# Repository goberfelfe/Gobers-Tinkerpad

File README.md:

# Gober's Tinkerpad
My Hackpad submission!

# About
This is my first hardware project, and it took me WEEKS to finish because I had absolutely no idea what I was doing. I had to restart so many times I almost gave up, but here we are!
# Schematic
I got a bit of help from my friend setting up the schematic. I wanted a LOT of buttons, and I had no idea how to make a matrix. it all worked out (hopefully!)

# PCB
The PCB is sort of crowded since I designed a case for my first attempt and had to restart multiple times. I didn't want to redo the case.

# CAD
Here is the case for the macropad with all the other parts. I used Onshape to make the case. You can open the Onshape document [here!](https://cad.onshape.com/documents/7796dfcd00a07795a78ec31b/w/0ed4cf9bd7f3ab11e0fad6be/e/c3fea92cde887115296eb8a5?renderMode=0&uiState=6991f48789cf1a8369e0d710)

# Firmware
I used kmk for the firmware. The oled displays what mode you're using when you change it, and any other buttons show a silly Gober face. There is also an idle animation.

# BOM
Materials I used:
- 16x Cherry MX switches
- 1x 0.91 inch OLED display
- 1x Xiao RP2040
- 16x 1N4148 Diodes
- 1x 3D printed case

# Credits
Thanks to [Thegreatmewer](https://github.com/Thegreatmewer), [this video by Digikey](https://youtu.be/WU59DkI3BpQ), and the Hack Club Slack for helping me out!

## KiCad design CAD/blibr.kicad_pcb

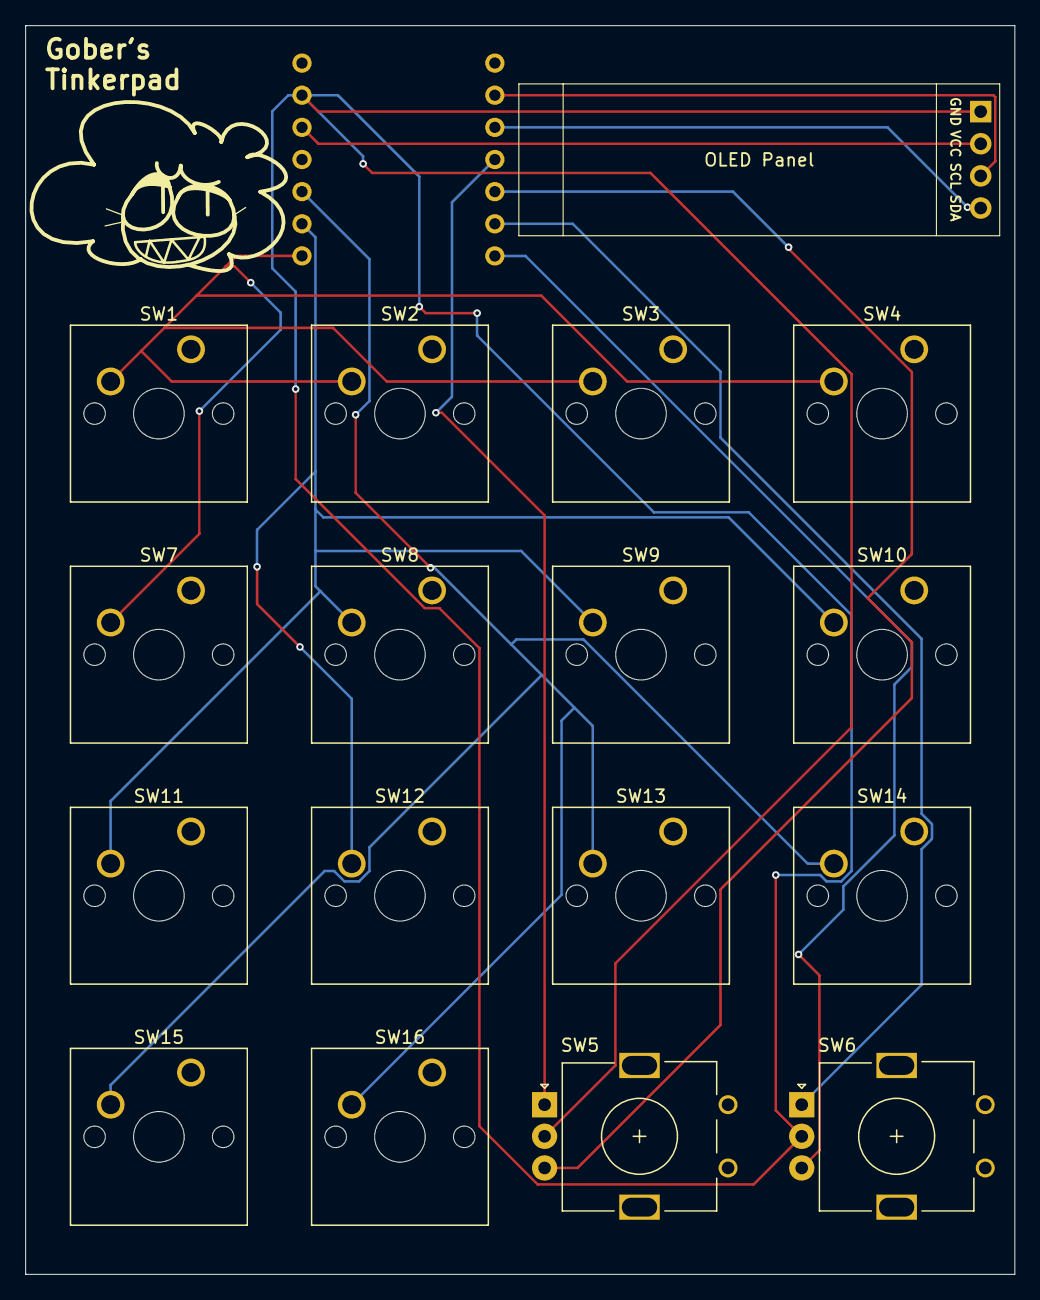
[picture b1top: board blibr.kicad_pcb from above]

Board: 2 copper layers, 78.2 x 98.7 mm, 18 parts (1 on the bottom side), 11 nets.

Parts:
J1: custom oled pins; awesome_oled
SW1, SW2, SW3, SW4, SW7, SW8, SW9, SW10, SW11, SW12, SW13, SW14, SW15, SW16: SW_Push; SW_Cherry_MX_1.00u_PCB
SW5, SW6: RotaryEncoder; RotaryEncoder_Alps_EC11E_Vertical_H20mm
U4: XIAO-RP2040-DIP

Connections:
GND: J1.1 (GND), SW5.C, SW6.C, U4.13 (GND)
unnamed: J1.3 (SCL), U4.2 (GPIO27/ADC1/A1)
unnamed: J1.4 (SDA), U4.3 (GPIO28/ADC2/A2)
unnamed: J1.2 (VCC), U4.12 (3V3)
unnamed: SW6.B, U4.7 (GPIO0/TX)
unnamed: SW1.2, SW2.2, SW3.2, SW4.2, SW7.2, U4.8 (GPIO1/RX)
unnamed: SW8.2, SW9.2, SW10.2, SW11.2, SW12.2, U4.9 (GPIO2/SCK)
unnamed: SW13.2, SW14.2, SW15.2, SW16.2, U4.10 (GPIO4/MISO)
unnamed: SW5.B, U4.5 (GPIO6/SDA)
unnamed: SW6.A, U4.6 (GPIO7/SCL)
unnamed: SW5.A, U4.4 (GPIO29/ADC3/A3)

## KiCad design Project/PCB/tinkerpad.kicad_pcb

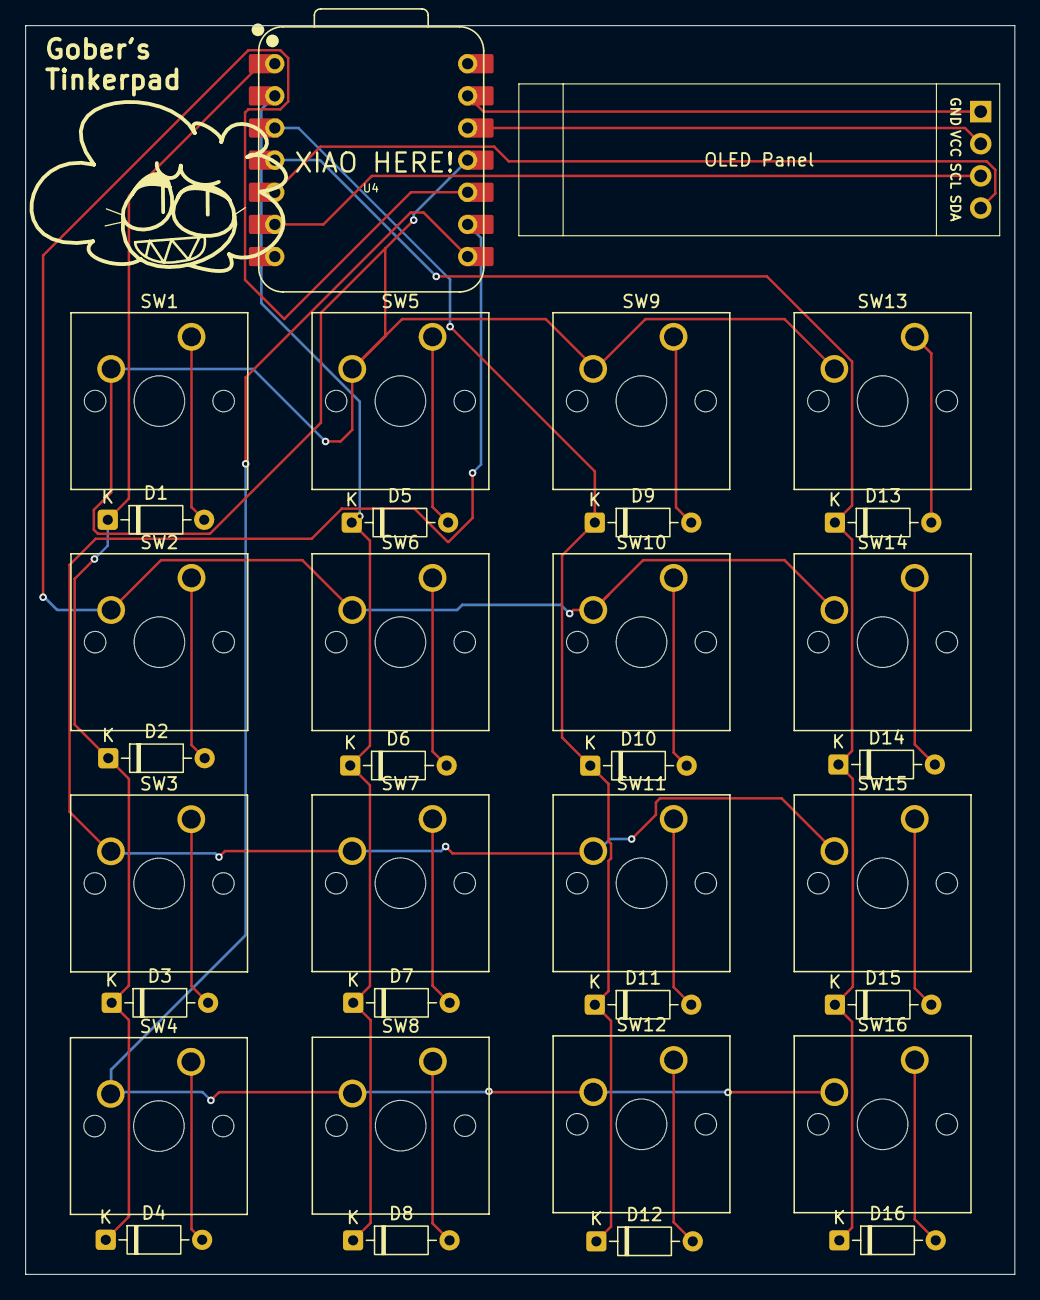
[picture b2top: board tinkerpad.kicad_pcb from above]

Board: 2 copper layers, 78.2 x 98.7 mm, 34 parts (0 on the bottom side), 28 nets.

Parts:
D1, D2, D3, D4, D5, D6, D7, D8, D9, D10, D11, D12, D13, D14, D15, D16: 1N4148; D_DO-35_SOD27_P7.62mm_Horizontal
J1: custom oled pins; awesome_oled
SW1, SW2, SW3, SW4, SW5, SW6, SW7, SW8, SW9, SW10, SW11, SW12, SW13, SW14, SW15, SW16: SW_Push; SW_Cherry_MX_1.00u_PCB
U4: XIAO-RP2040-DIP

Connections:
COL 1: SW1.2, SW5.2, SW9.2, SW13.2, U4.11 (GPIO3/MOSI)
COL 2: SW2.2, SW6.2, SW10.2, SW14.2, U4.10 (GPIO4/MISO)
COL 3: SW3.2, SW7.2, SW11.2, SW15.2, U4.9 (GPIO2/SCK)
COL 4: SW4.2, SW8.2, SW12.2, SW16.2, U4.8 (GPIO1/RX)
GND: J1.1 (GND), U4.13 (GND)
unnamed: D1.2 (A), SW1.1
unnamed: D2.2 (A), SW2.1
unnamed: D3.2 (A), SW3.1
unnamed: D4.2 (A), SW4.1
unnamed: D5.2 (A), SW5.1
unnamed: D6.2 (A), SW6.1
unnamed: D7.2 (A), SW7.1
unnamed: D8.2 (A), SW8.1
unnamed: D9.2 (A), SW9.1
unnamed: D10.2 (A), SW10.1
unnamed: D11.2 (A), SW11.1
unnamed: D12.2 (A), SW12.1
unnamed: D13.2 (A), SW13.1
unnamed: D14.2 (A), SW14.1
unnamed: D15.2 (A), SW15.1
unnamed: D16.2 (A), SW16.1
ROW 1: D1.1 (K), D2.1 (K), D3.1 (K), D4.1 (K), U4.1 (GPIO26/ADC0/A0)
ROW 2: D5.1 (K), D6.1 (K), D7.1 (K), D8.1 (K), U4.2 (GPIO27/ADC1/A1)
ROW 3: D9.1 (K), D10.1 (K), D11.1 (K), D12.1 (K), U4.3 (GPIO28/ADC2/A2)
ROW 4: D13.1 (K), D14.1 (K), D15.1 (K), D16.1 (K), U4.4 (GPIO29/ADC3/A3)
SCL: J1.3 (SCL), U4.6 (GPIO7/SCL)
SDA: J1.4 (SDA), U4.5 (GPIO6/SDA)
VCC: J1.2 (VCC), U4.12 (3V3)

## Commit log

2026-01-30 Add files via upload
    cool, there's files now!
2026-01-30 Rename Screenshot 2026-01-29 211204.png to pcb.png
2026-01-30 Rename Screenshot 2026-01-29 204610.png to schematicpng
2026-01-30 Rename Screenshot 2026-01-29 202640.png to case1.png
2026-01-30 Rename Screenshot 2026-01-29 202625.png to case2.png
2026-01-30 testing github caca
2026-01-30 simga.
2026-01-30 move blibr.kicad_pcb
2026-01-30 Rename blibr.kicad_pro to CAD/blibr.kicad_pro
2026-01-30 Rename blibr.kicad_pro to blibr.kicad_pro
2026-01-30 Rename Gober's Tinkerpad.step to CAD/Gober's Tinkerpad.step
2026-01-30 Add placeholder text to glgh file
2026-01-30 Rename schematicpng to schematic.png
2026-01-30 Rename case1.png to Assets/case1.png
2026-01-30 Rename case2.png to Assets/case2.png
2026-01-30 Rename pcb.png to Assets/pcb.png
2026-01-30 Rename schematic.png to Assets/schematic.png
2026-02-02 Revise README with WIP title and schematic update
    Updated project title to indicate work in progress and removed schematic image.
2026-02-02 the
    the
2026-02-14 Enhance README with project details and credits
    Added detailed project description, schematic, PCB, firmware plans, BOM, and credits.
2026-02-14 Update credits section with proper link formatting
2026-02-14 Update credits with a link to Digikey's video
2026-02-14 Revise BOM section in README.md
    Updated the Bill of Materials (BOM) section to reflect changes.
2026-02-14 Fix formatting in BOM section of README
    Updated BOM section formatting in README.
2026-02-14 Pictures.
2026-02-14 Rename Screenshot 2026-02-07 200007.png to schematic.png
2026-02-14 Rename Screenshot 2026-02-14 121441.png to assembly.png
2026-02-14 Rename Screenshot 2026-02-09 164151.png to pcb.png
2026-02-14 NUH UHH
2026-02-14 more files.. (my head hurts)
2026-02-14 Create placeholder2
2026-02-14 Update OLED display specification in README
2026-02-14 Fix image paths and add CAD section in README
    Updated image paths to use 'Assets' directory and added CAD section with case image.
2026-02-14 Fix image paths in README.md
    Updated image paths in README to correct locations.
2026-02-14 Change case image in README
    Updated the case image for Gober's Tinkerpad.
2026-02-14 Upload CORRECT case screenshot.
2026-02-14 Rename Screenshot 2026-02-14 130429.png to case1.png
2026-02-14 hey bud let's try that again.
2026-02-14 one more time before i bite someone.
    IT KEEPS CHANGING THE PICTURE WHEN I RENAME IT I'M SORRY
2026-02-14 Rename Screenshot 2026-02-14 130429.png to case2.png
2026-02-14 Change case image for Gober's Tinkerpad
    Updated the case image for Gober's Tinkerpad in the README.
2026-02-14 Rename tinkerpad case bottom.step to tinkerpad case bottom.step
2026-02-14 Rename tinkerpad case top.step to tinkerpad case top.step
2026-02-14 Rename tinkerpad.kicad_pro to tinkerpad.kicad_pro
2026-02-14 Rename tinkerpad.zip to PCB/tinkerpad.zip
2026-02-14 Update and rename glgh to WIP
2026-02-14 Rename CAD/Gober's Tinkerpad [CASE].step to Project/CAD/Gober's Tinkerpad [CASE].step
2026-02-14 Rename CAD/Gober's Tinkerpad.step to Project/CAD/Gober's Tinkerpad.step
2026-02-14 Create balls2
2026-02-14 Rename PCB/tinkerpad.kicad_pro to Project/PCB/tinkerpad.kicad_pro
2026-02-14 Rename tinkerpad.zip to tinkerpad.zip
2026-02-14 Update firmware section
2026-02-14 Add main.py
2026-02-14 Add Onshape link
2026-02-14 Rename tinkerpad.zip to gerbers.zip
2026-02-14 Rename Screenshot 2026-02-14 180309.png to assembly1.png
2026-02-14 Rename Screenshot 2026-02-14 180251.png to assembly2.png
2026-02-14 Rename Screenshot 2026-02-14 180218.png to assembly3.png
2026-02-15 Add Tinkerpad full assembly file
